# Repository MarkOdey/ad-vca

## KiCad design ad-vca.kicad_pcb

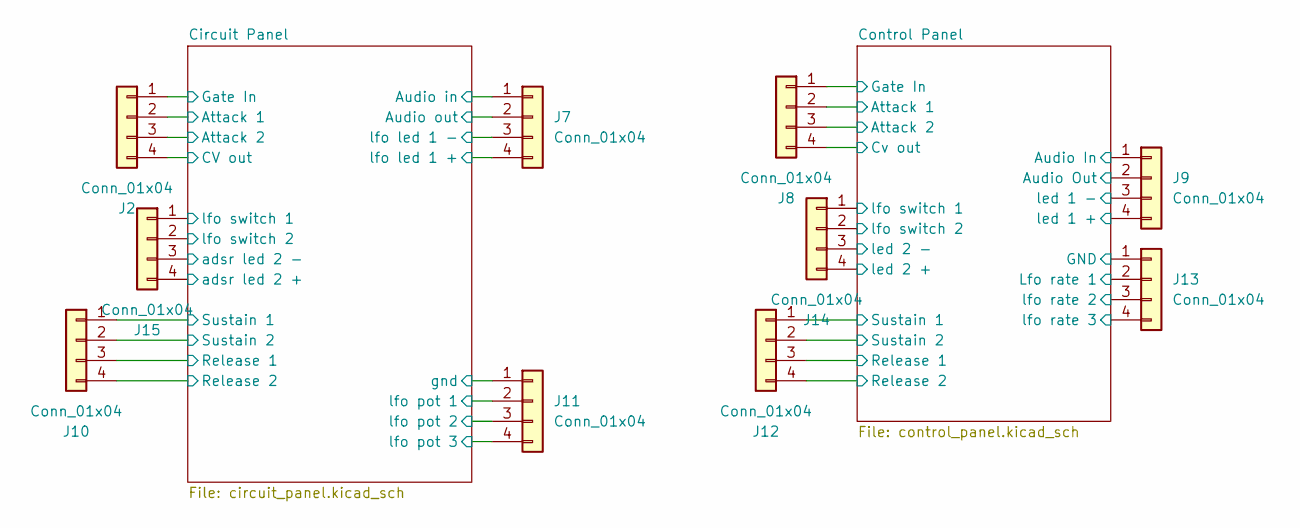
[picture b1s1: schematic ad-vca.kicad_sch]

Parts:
J2, J7, J8, J9, J10, J11, J12, J13, J14, J15: Conn_01x04; PinHeader_1x04_P2.54mm_Vertical

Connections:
+12V: J7.4, J15.4; also elsewhere on the board
/Circuit Panel/Attack 1: J2.2; also elsewhere on the board
/Circuit Panel/Attack 2: J2.3, J10.4; also elsewhere on the board
/Circuit Panel/Audio in: J7.1; also elsewhere on the board
/Circuit Panel/Audio out: J7.2; also elsewhere on the board
/Circuit Panel/CV out: J2.4; also elsewhere on the board
/Circuit Panel/Gate In: J2.1; also elsewhere on the board
/Circuit Panel/Release 1: J10.3; also elsewhere on the board
/Circuit Panel/Sustain 1: J10.1; also elsewhere on the board
/Circuit Panel/Sustain 2: J10.2; also elsewhere on the board
/Circuit Panel/adsr led 2 -: J15.3; also elsewhere on the board
/Circuit Panel/lfo led 1 -: J7.3, J15.1; also elsewhere on the board
/Circuit Panel/lfo pot 1: J11.2, J15.2; also elsewhere on the board
/Circuit Panel/lfo pot 2: J11.3; also elsewhere on the board
/Control Panel/Attack 1: J8.2; also elsewhere on the board
/Control Panel/Attack 2: J8.3; also elsewhere on the board
/Control Panel/Audio In: J9.1; also elsewhere on the board
/Control Panel/Audio Out: J9.2; also elsewhere on the board
/Control Panel/Cv out: J8.4; also elsewhere on the board
/Control Panel/GND: J13.1; also elsewhere on the board
/Control Panel/Gate In: J8.1; also elsewhere on the board
/Control Panel/Lfo rate 1: J13.2; also elsewhere on the board
/Control Panel/Release 1: J12.3; also elsewhere on the board
/Control Panel/Release 2: J12.4; also elsewhere on the board
/Control Panel/Sustain 1: J12.1; also elsewhere on the board
/Control Panel/Sustain 2: J12.2; also elsewhere on the board
/Control Panel/led 1 +: J9.4; also elsewhere on the board
/Control Panel/led 1 -: J9.3; also elsewhere on the board
/Control Panel/led 2 +: J14.4; also elsewhere on the board
/Control Panel/led 2 -: J14.3; also elsewhere on the board
/Control Panel/lfo rate 2: J13.3; also elsewhere on the board
/Control Panel/lfo rate 3: J13.4; also elsewhere on the board
/Control Panel/lfo switch 1: J14.1; also elsewhere on the board
/Control Panel/lfo switch 2: J14.2; also elsewhere on the board
GND: J11.1, J11.4; also elsewhere on the board

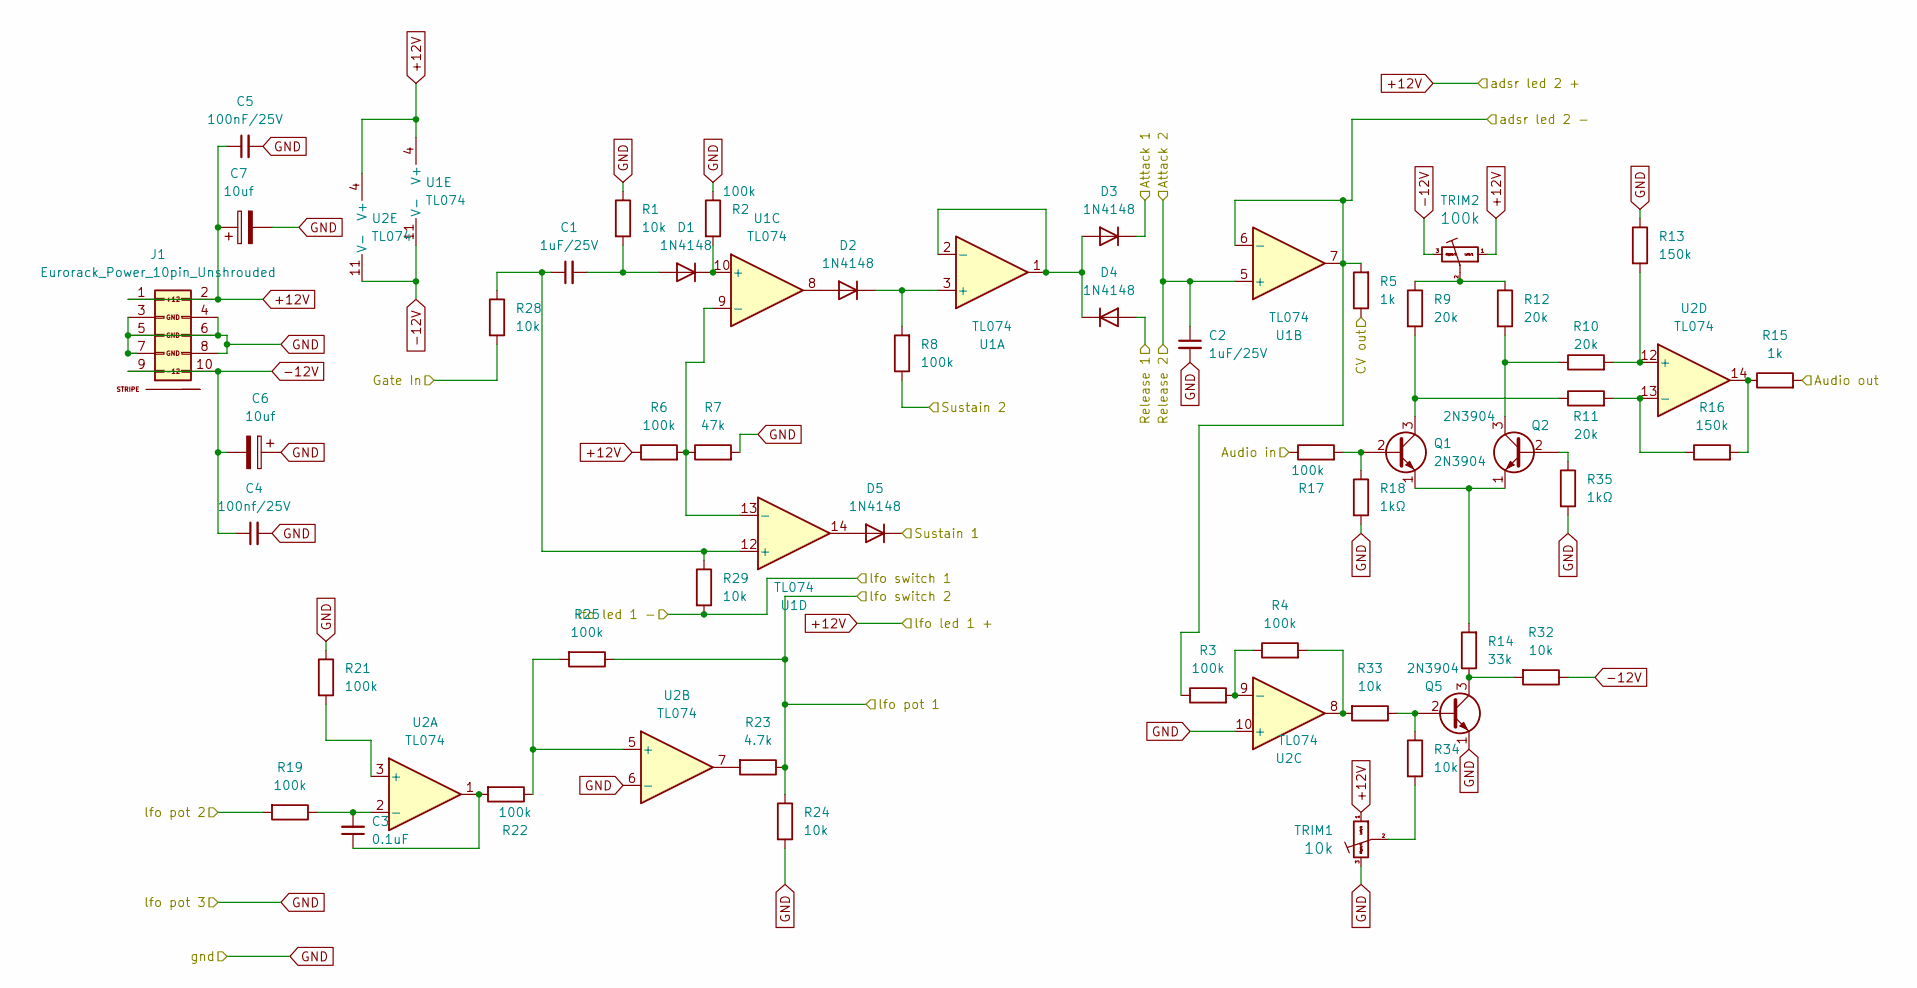
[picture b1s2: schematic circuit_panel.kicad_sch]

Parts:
C1, C2: 1uF_0603_25V; C_Disc_D3.0mm_W1.6mm_P2.50mm; Part Number GRM188R61E105KA12D; JLCPCB ID C15849
C3: 0.1uF_0603_16V; C_Disc_D3.0mm_W1.6mm_P2.50mm; Part Number 0603YC104KAT2A; JLCPCB ID C14663
C4, C5: 1uF_0603_25V; C_Disc_D3.8mm_W2.6mm_P2.50mm; Part Number GRM188R61E105KA12D; JLCPCB ID C15849
C6, C7: 10uf; CP_Radial_D4.0mm_P2.00mm
D1, D2, D3, D4, D5: 1N4148; D_DO-35_SOD27_P7.62mm_Horizontal
J1: Eurorack_Power_10pin_Unshrouded; Pins_2x05_2.54mm_TH_Europower; Part Number 1-1002FBV0T
Q1, Q2, Q5: 2N3904; TO-92_Inline
R1, R10, R11, R14, R28, R29, R32, R33, R34: 10k_0603; R_Axial_DIN0207_L6.3mm_D2.5mm_P7.62mm_Horizontal; Part Number RC0603FR-0710KL; JLCPCB ID C25804
R2, R6, R8, R9, R12, R17, R19, R22, R25: 100k_0603; R_Axial_DIN0207_L6.3mm_D2.5mm_P7.62mm_Horizontal; Part Number RC0603FR-07100KL; JLCPCB ID C25803
R3: 200k_0603; R_Axial_DIN0207_L6.3mm_D2.5mm_P7.62mm_Horizontal; Part Number RC0603FR-07200KL; JLCPCB ID C25811
R4: 33k_0603; R_Axial_DIN0207_L6.3mm_D2.5mm_P7.62mm_Horizontal; Part Number RC0603FR-0733KL; JLCPCB ID C4216
R5, R15, R21: 1k_0603; R_Axial_DIN0207_L6.3mm_D2.5mm_P7.62mm_Horizontal; Part Number RC0603FR-071KL; JLCPCB ID C21190
R7, R23: 47k_0603; R_Axial_DIN0207_L6.3mm_D2.5mm_P7.62mm_Horizontal; Part Number RC0603FR-0747KL; JLCPCB ID C25819
R13, R16: 470k_0603; R_Axial_DIN0207_L6.3mm_D2.5mm_P7.62mm_Horizontal; Part Number RC0603FR-0747KL; JLCPCB ID C23178
R18, R35: 100_0603; R_Axial_DIN0207_L6.3mm_D2.5mm_P7.62mm_Horizontal; Part Number RC0603FR-07100RL; JLCPCB ID C22775
R24: 10k_0402; R_Axial_DIN0207_L6.3mm_D2.5mm_P7.62mm_Horizontal; Part Number RT0402FRE0710KL
TRIM1, TRIM2: TrimPot_T73YEt_10k; Potentiometer_Bourns_3296W_Vertical; Part Number T73YE103KT20
U1, U2: TL074; DIP-14_W7.62mm

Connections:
+12V: C5.1, C7.1, J1.1 (+12V), J1.2 (+12V), R6.1, TRIM1.1 (Left), TRIM2.1 (Left), U1.4 (V+), U2.4 (V+); also elsewhere on the board
-12V: C4.1, C6.2, J1.9 (-12V), J1.10 (-12V), R32.1, TRIM2.3 (Right), U1.11 (V-), U2.11 (V-)
/Circuit Panel/Attack 1: D3.1 (K); also elsewhere on the board
/Circuit Panel/Attack 2: C2.1, U1.5 (+); also elsewhere on the board
/Circuit Panel/Audio in: R17.1; also elsewhere on the board
/Circuit Panel/Audio out: R15.2; also elsewhere on the board
/Circuit Panel/CV out: R5.1; also elsewhere on the board
/Circuit Panel/Gate In: R28.2; also elsewhere on the board
/Circuit Panel/Release 1: D4.2 (A); also elsewhere on the board
/Circuit Panel/Sustain 1: D5.1 (K); also elsewhere on the board
/Circuit Panel/Sustain 2: R8.1; also elsewhere on the board
/Circuit Panel/adsr led 2 -: R3.1, R5.2, U1.6 (-), U1.7; also elsewhere on the board
/Circuit Panel/lfo led 1 -: R29.2; also elsewhere on the board
/Circuit Panel/lfo pot 1: R23.1, R24.1, R25.1; also elsewhere on the board
/Circuit Panel/lfo pot 2: R19.2; also elsewhere on the board
GND: C2.2, C4.2, C5.2, C6.1, C7.2, J1.3 (GND), J1.4 (GND), J1.5 (GND), J1.6 (GND), J1.7 (GND), J1.8 (GND), Q5.1 (E), R1.1, R2.1, R7.2, R13.1, R18.2, R21.1, R24.2, R35.2, TRIM1.3 (Right), U2.6 (-), U2.10 (+); also elsewhere on the board
unnamed: C3.1, R22.2, U2.1
unnamed: C1.2, D1.2 (A), R1.2
unnamed: D1.1 (K), R2.2, U1.10 (+)
unnamed: D2.2 (A), U1.8
unnamed: D2.1 (K), R8.2, U1.3 (+)
unnamed: D3.2 (A), D4.1 (K), U1.1, U1.2 (-)
unnamed: D5.2 (A), U1.14
unnamed: Q1.2 (B), R17.2, R18.1
unnamed: Q1.3 (C), R9.2, R11.1
unnamed: Q1.1 (E), Q2.1 (E), R14.2
unnamed: Q2.2 (B), R35.1
unnamed: Q2.3 (C), R10.1, R12.2
unnamed: Q5.2 (B), R33.1, R34.1
unnamed: Q5.3 (C), R14.1, R32.2
unnamed: R15.1, R16.2, U2.14
unnamed: R23.2, U2.7
unnamed: R4.2, R33.2, U2.8
unnamed: R34.2, TRIM1.2 (Center)
unnamed: R9.1, R12.1, TRIM2.2 (Center)
unnamed: R6.2, R7.1, U1.9 (-), U1.13 (-)
unnamed: C1.1, R28.1, R29.1, U1.12 (+)
unnamed: R21.2, U2.3 (+)
unnamed: C3.2, R19.1, U2.2 (-)
unnamed: R22.1, R25.2, U2.5 (+)
unnamed: R3.2, R4.1, U2.9 (-)
unnamed: R10.2, R13.2, U2.12 (+)
unnamed: R11.2, R16.1, U2.13 (-)

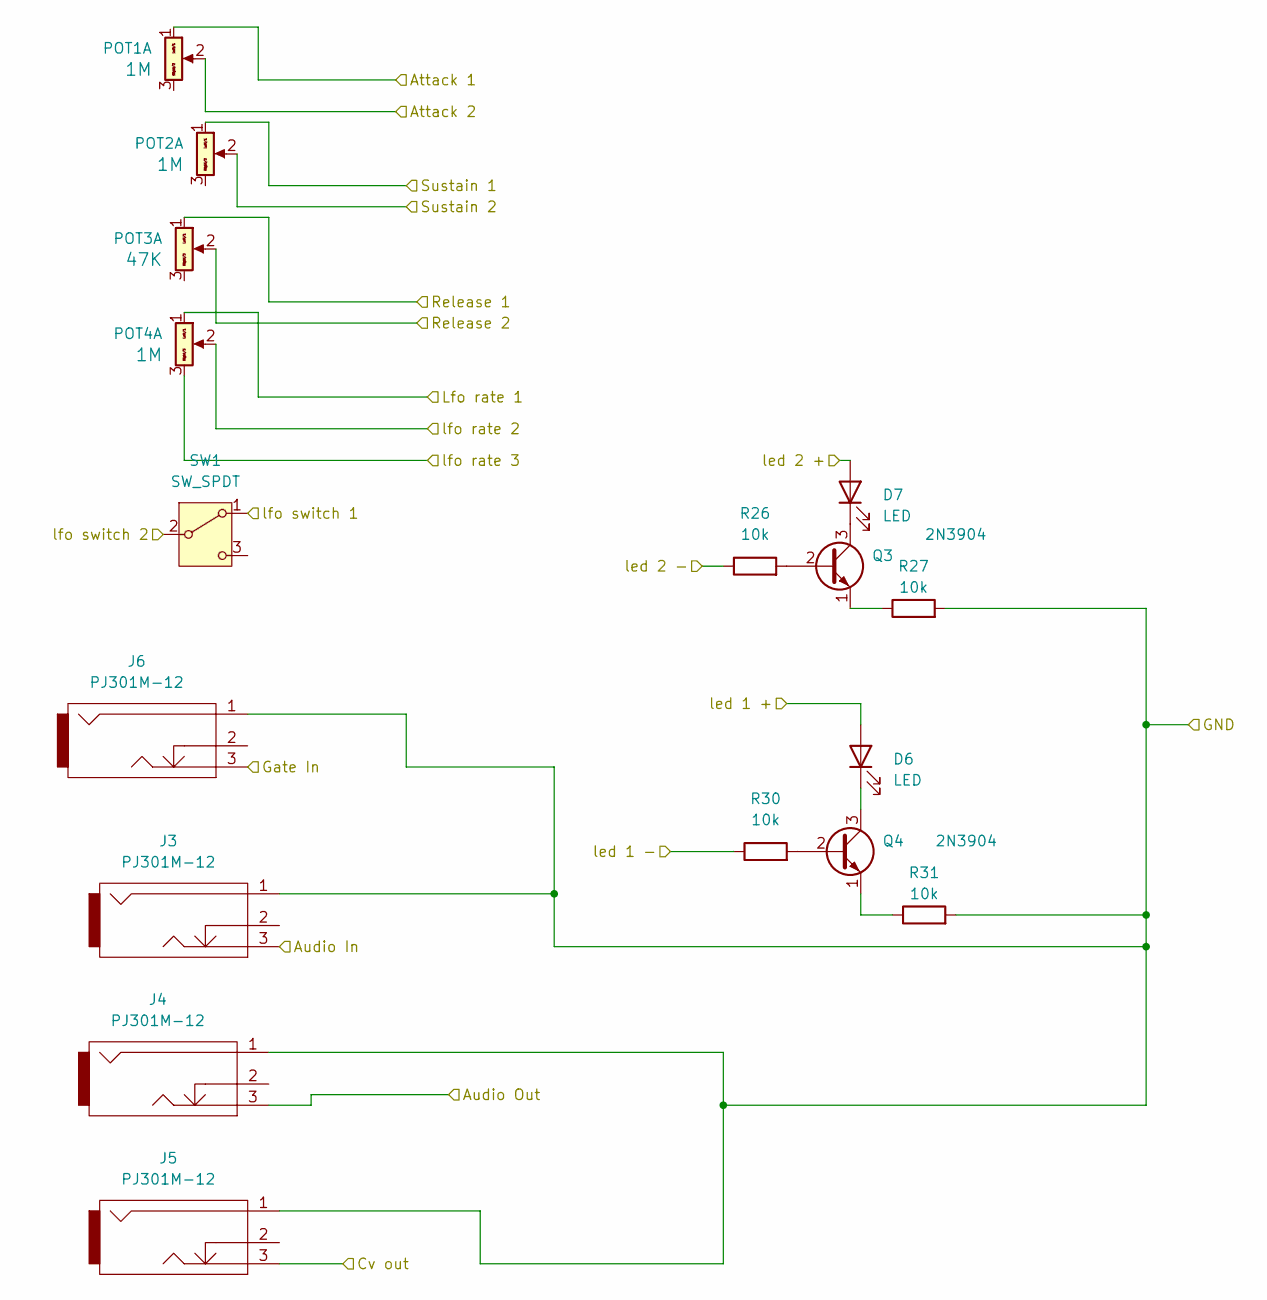
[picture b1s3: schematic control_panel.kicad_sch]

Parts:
D6, D7: LED; LED3mm
J3, J4, J5, J6: PJ301M-12
POT1, POT2, POT4: 9mm_NoDet_1M_Knurled_Lined; Pot_9mm_DShaft; Part Number RV16AF-4A-15FW-B100K-3
POT3: 9mm_NoDet_47K_Knurled_Lined; Pot_9mm_DShaft; Part Number RV16AF-4A-15FW-B47k-3
Q3, Q4: 2N3904; TO-92_Inline
R26, R27, R30, R31: 10k_0402; R_Axial_DIN0207_L6.3mm_D2.5mm_P7.62mm_Horizontal; Part Number RT0402FRE0710KL
SW1: SW_SPDT; spdt - toggle switch

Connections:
/Control Panel/Attack 1: POT1.1 (Left); also elsewhere on the board
/Control Panel/Attack 2: POT1.2 (Center); also elsewhere on the board
/Control Panel/Audio In: J3.3; also elsewhere on the board
/Control Panel/Audio Out: J4.3; also elsewhere on the board
/Control Panel/Cv out: J5.3; also elsewhere on the board
/Control Panel/GND: J3.1, J4.1, J5.1, J6.1, R27.2, R31.2; also elsewhere on the board
/Control Panel/Gate In: J6.3; also elsewhere on the board
/Control Panel/Lfo rate 1: POT4.1 (Left); also elsewhere on the board
/Control Panel/Release 1: POT3.1 (Left); also elsewhere on the board
/Control Panel/Release 2: POT3.2 (Center); also elsewhere on the board
/Control Panel/Sustain 1: POT2.1 (Left); also elsewhere on the board
/Control Panel/Sustain 2: POT2.2 (Center); also elsewhere on the board
/Control Panel/led 1 +: D6.2 (A); also elsewhere on the board
/Control Panel/led 1 -: R30.1; also elsewhere on the board
/Control Panel/led 2 +: D7.2 (A); also elsewhere on the board
/Control Panel/led 2 -: R26.1; also elsewhere on the board
/Control Panel/lfo rate 2: POT4.2 (Center); also elsewhere on the board
/Control Panel/lfo rate 3: POT4.3 (Right); also elsewhere on the board
/Control Panel/lfo switch 1: SW1.1 (A); also elsewhere on the board
/Control Panel/lfo switch 2: SW1.2 (B); also elsewhere on the board
unnamed: D6.1 (K), Q4.3 (C)
unnamed: D7.1 (K), Q3.3 (C)
unnamed: Q3.2 (B), R26.2
unnamed: Q3.1 (E), R27.1
unnamed: Q4.2 (B), R30.2
unnamed: Q4.1 (E), R31.1

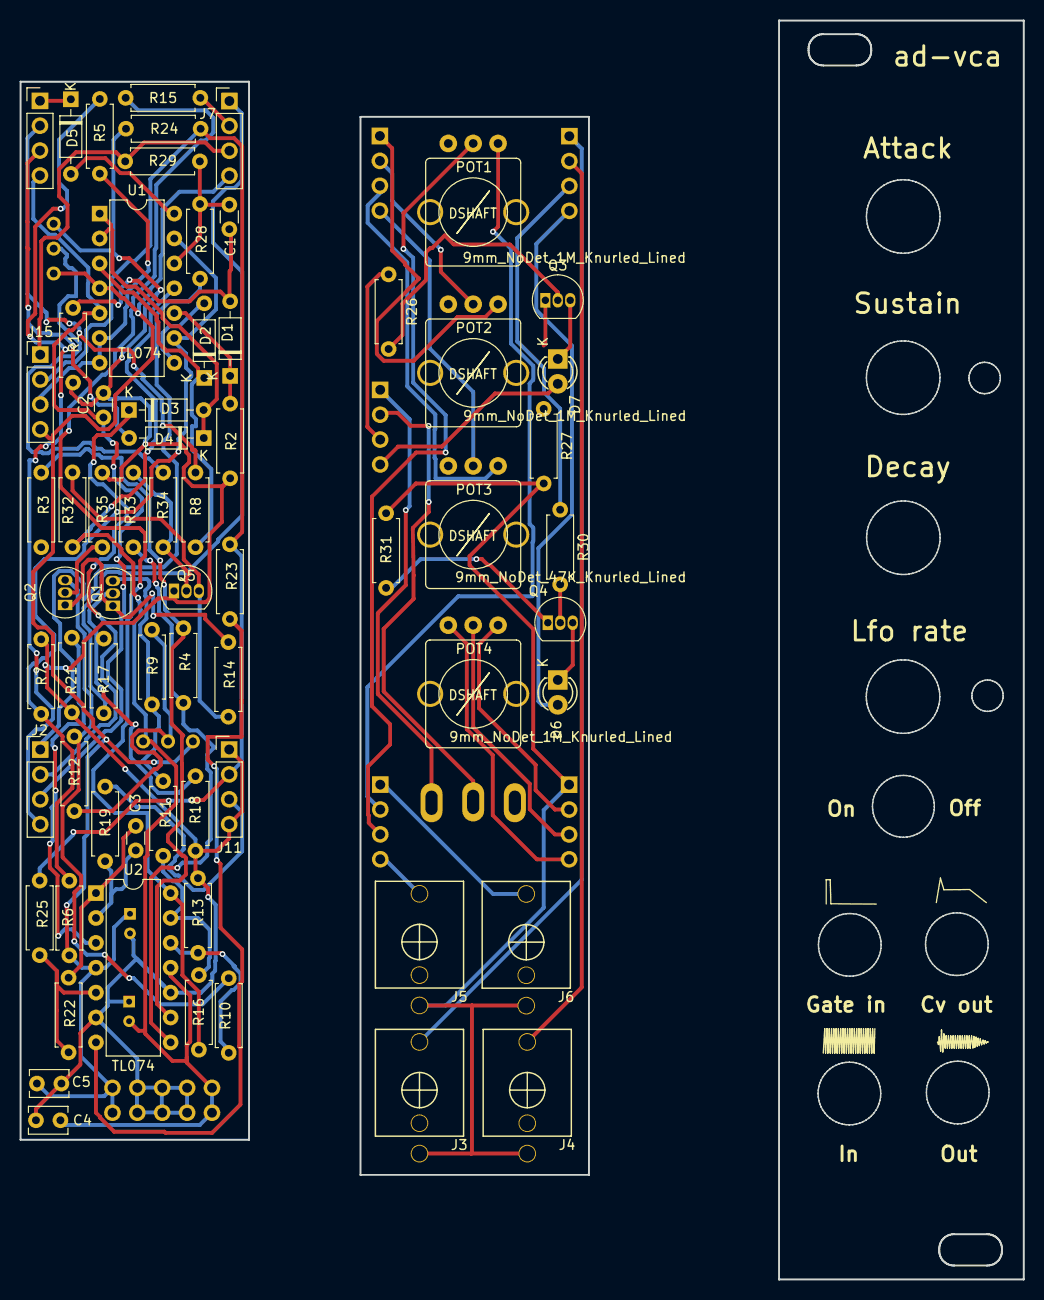
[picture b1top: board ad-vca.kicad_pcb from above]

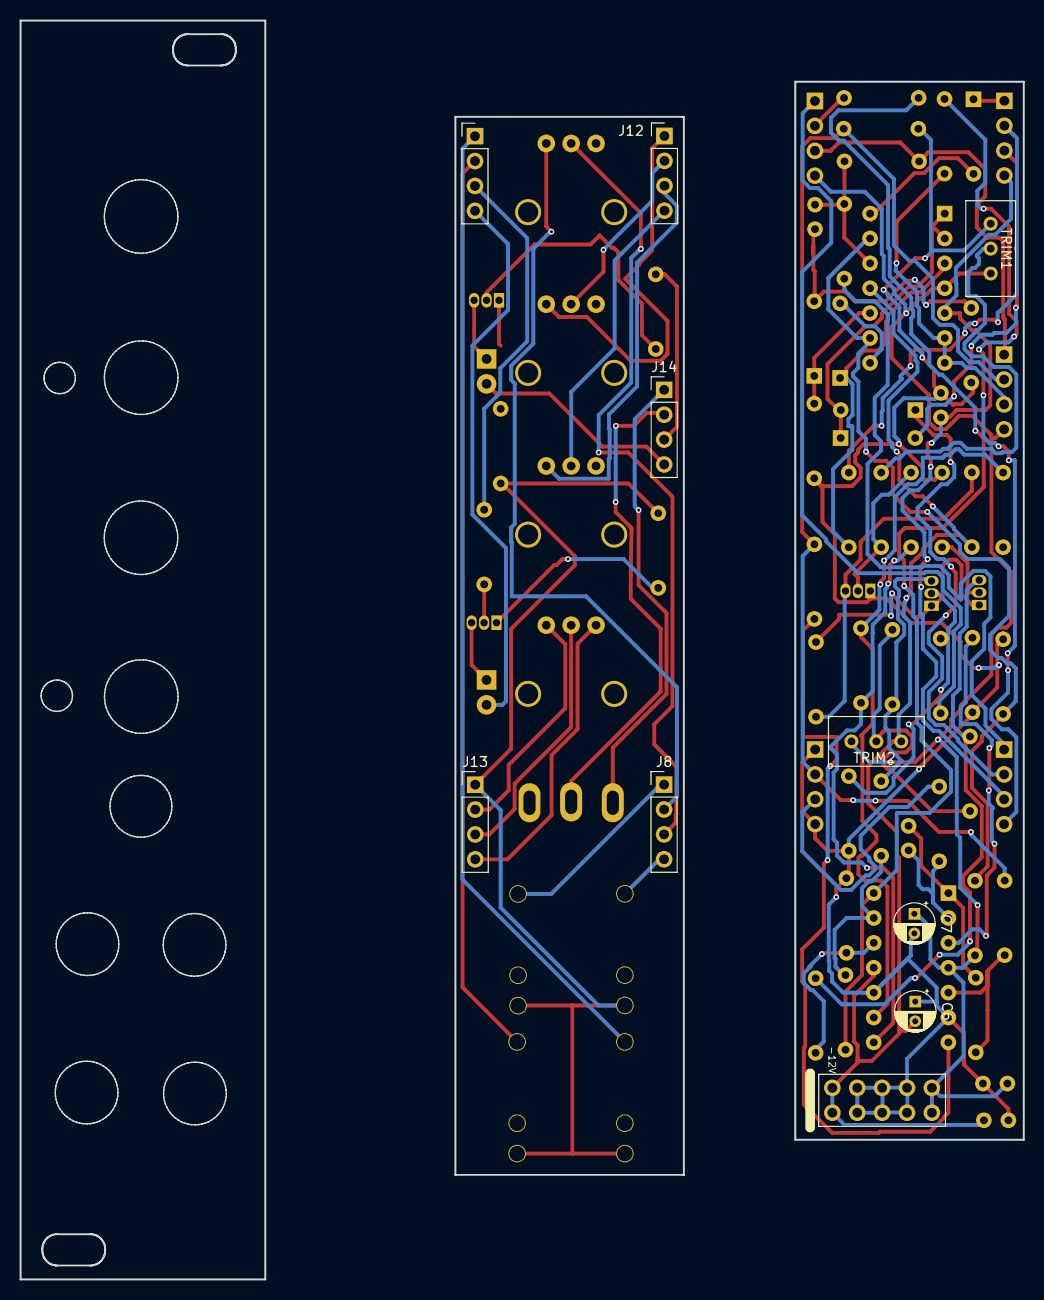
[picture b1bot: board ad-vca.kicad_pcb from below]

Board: 2 copper layers, 102.4 x 128.5 mm, 77 parts (10 on the bottom side), 69 nets.

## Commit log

2024-10-06 First print round
2024-10-20 Fixed bad tracing and reviewed circuit design
